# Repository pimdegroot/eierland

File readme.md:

This is a prototype project and has been put online to help somebody out. There are known bugs and it is not recommend to replicate the board. At one point a new rev might appear.

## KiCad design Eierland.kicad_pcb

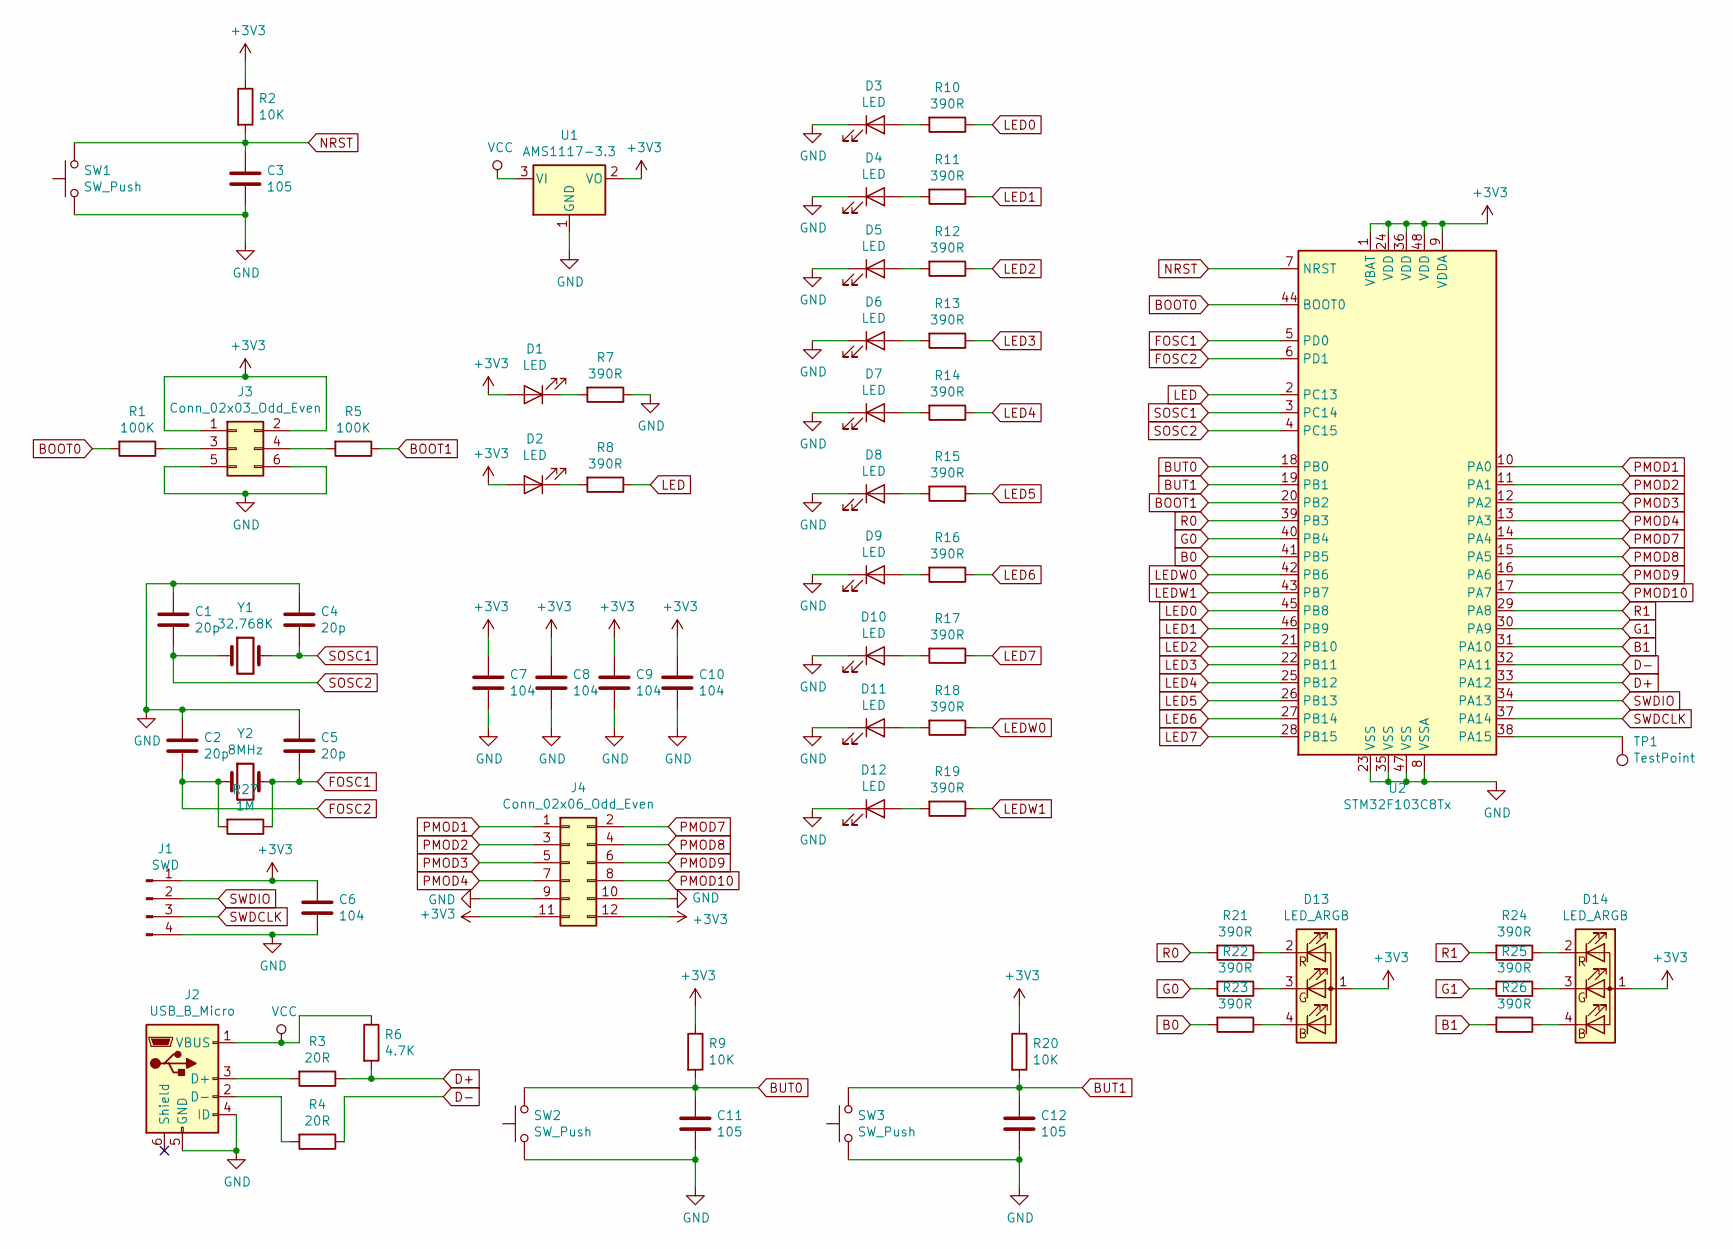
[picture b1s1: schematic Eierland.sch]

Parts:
C1, C2, C4, C5: 20p; C_0805_2012Metric
C3, C11, C12: 105; C_0805_2012Metric
C6, C7, C8, C9, C10: 104; C_0805_2012Metric
D1, D2, D3, D4, D5, D6, D7, D8, D9, D10, D11, D12: LED; LED_1206_3216Metric
D13, D14: LED_ARGB; LED_Cree-PLCC4_3.2x2.8mm_CCW
J1: SWD; PinHeader_1x04_P2.54mm_Horizontal
J2: USB_B_Micro; USB_Micro-B_GCT_USB3076-30-A
J3: Conn_02x03_Odd_Even; PinHeader_2x03_P2.54mm_Vertical
J4: Conn_02x06_Odd_Even; PinHeader_2x06_P2.54mm_Horizontal
R1, R5: 100K; R_0805_2012Metric
R2, R9, R20: 10K; R_0805_2012Metric
R3, R4: 20R; R_0805_2012Metric
R6: 4.7K; R_0805_2012Metric
R7, R8, R10, R11, R12, R13, R14, R15, R16, R17, R18, R19, R21, R22, R23, R24, R25, R26: 390R; R_0805_2012Metric
R27: 1M; R_0805_2012Metric
SW1, SW2, SW3: SW_Push; SW_SPST_EVPBF
TP1: TestPoint; TestPoint_Pad_D1.0mm
U1: AMS1117-3.3; SOT-223-3_TabPin2
U2: STM32F103C8Tx; LQFP-48_7x7mm_P0.5mm
Y1: 32.768K; Crystal_SMD_3215-2Pin_3.2x1.5mm
Y2: 8MHz; Crystal_SMD_HC49-SD

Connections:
+3V3: C6.1, C7.1, C8.1, C9.1, C10.1, D1.2 (A), D2.2 (A), D13.1 (A), D14.1 (A), J1.1, J3.1, J3.2, J4.11, J4.12, R2.1, R9.1, R20.1, U1.2 (VO), U2.1 (VBAT), U2.9 (VDDA), U2.24 (VDD), U2.36 (VDD), U2.48 (VDD)
B0: R23.2, U2.41 (PB5)
B1: R26.2, U2.31 (PA10)
BOOT0: R1.2, U2.44 (BOOT0)
BOOT1: R5.1, U2.20 (PB2)
BUT0: C11.1, R9.2, SW2.2, U2.18 (PB0)
BUT1: C12.1, R20.2, SW3.2, U2.19 (PB1)
D+: R3.1, R6.2, U2.33 (PA12)
D-: R4.1, U2.32 (PA11)
FOSC1: C5.2, R27.1, U2.5 (PD0), Y2.2
FOSC2: C2.2, R27.2, U2.6 (PD1), Y2.1
G0: R22.2, U2.40 (PB4)
G1: R25.2, U2.30 (PA9)
GND: C1.1, C2.1, C3.2, C4.1, C5.1, C6.2, C7.2, C8.2, C9.2, C10.2, C11.2, C12.2, D3.1 (K), D4.1 (K), D5.1 (K), D6.1 (K), D7.1 (K), D8.1 (K), D9.1 (K), D10.1 (K), D11.1 (K), D12.1 (K), J1.4, J2.4 (ID), J2.5 (GND), J3.5, J3.6, J4.9, J4.10, R7.1, SW1.1, SW2.1, SW3.1, U1.1 (GND), U2.8 (VSSA), U2.23 (VSS), U2.35 (VSS), U2.47 (VSS)
LED: R8.1, U2.2 (PC13)
LED0: R10.1, U2.45 (PB8)
LED1: R11.1, U2.46 (PB9)
LED2: R12.1, U2.21 (PB10)
LED3: R13.1, U2.22 (PB11)
LED4: R14.1, U2.25 (PB12)
LED5: R15.1, U2.26 (PB13)
LED6: R16.1, U2.27 (PB14)
LED7: R17.1, U2.28 (PB15)
LEDW0: R18.1, U2.42 (PB6)
LEDW1: R19.1, U2.43 (PB7)
NRST: C3.1, R2.2, SW1.2, U2.7 (NRST)
unnamed: D1.1 (K), R7.2
unnamed: D2.1 (K), R8.2
unnamed: D3.2 (A), R10.2
unnamed: D4.2 (A), R11.2
unnamed: D5.2 (A), R12.2
unnamed: D6.2 (A), R13.2
unnamed: D7.2 (A), R14.2
unnamed: D8.2 (A), R15.2
unnamed: D9.2 (A), R16.2
unnamed: D10.2 (A), R17.2
unnamed: D11.2 (A), R18.2
unnamed: D12.2 (A), R19.2
unnamed: D13.2 (RK), R21.1
unnamed: D13.3 (GK), R22.1
unnamed: D13.4 (BK), R23.1
unnamed: D14.2 (RK), R24.1
unnamed: D14.3 (GK), R25.1
unnamed: D14.4 (BK), R26.1
unnamed: J2.2 (D-), R4.2
unnamed: J2.3 (D+), R3.2
unnamed: J3.3, R1.1
unnamed: J3.4, R5.2
unnamed: TP1.1, U2.38 (PA15)
PMOD1: J4.1, U2.10 (PA0)
PMOD2: J4.3, U2.11 (PA1)
PMOD3: J4.5, U2.12 (PA2)
PMOD4: J4.7, U2.13 (PA3)
PMOD7: J4.2, U2.14 (PA4)
PMOD8: J4.4, U2.15 (PA5)
PMOD9: J4.6, U2.16 (PA6)
PMOD10: J4.8, U2.17 (PA7)
R0: R21.2, U2.39 (PB3)
R1: R24.2, U2.29 (PA8)
SOSC1: C4.2, U2.3 (PC14), Y1.2
SOSC2: C1.2, U2.4 (PC15), Y1.1
SWDCLK: J1.3, U2.37 (PA14)
SWDIO: J1.2, U2.34 (PA13)
VCC: J2.1 (VBUS), R6.1, U1.3 (VI)

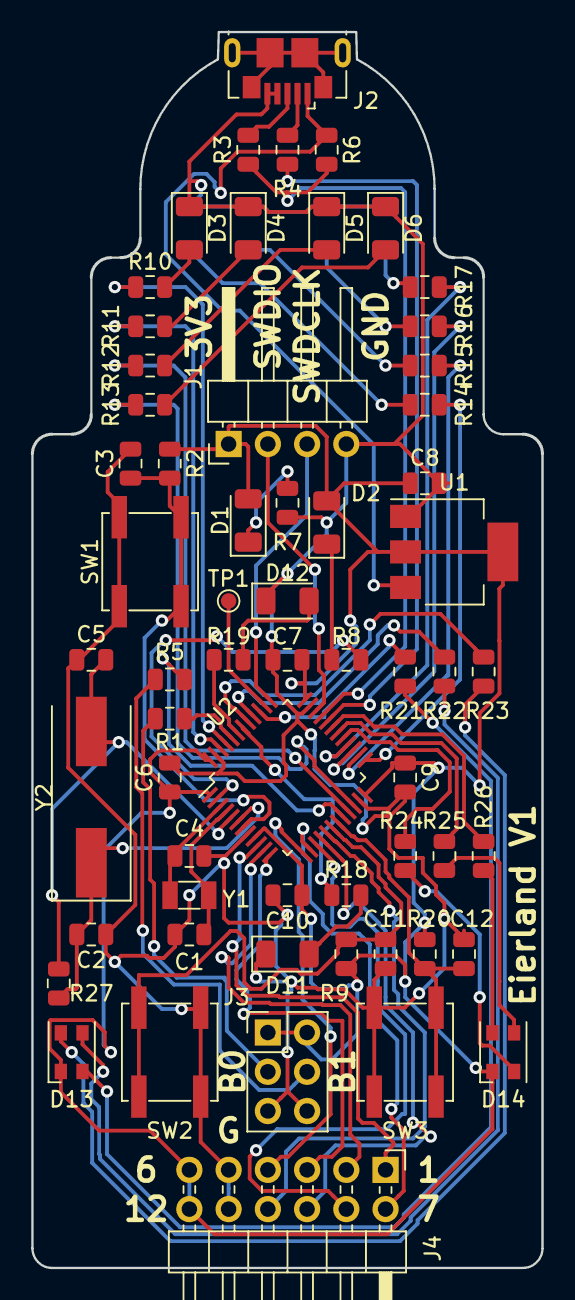
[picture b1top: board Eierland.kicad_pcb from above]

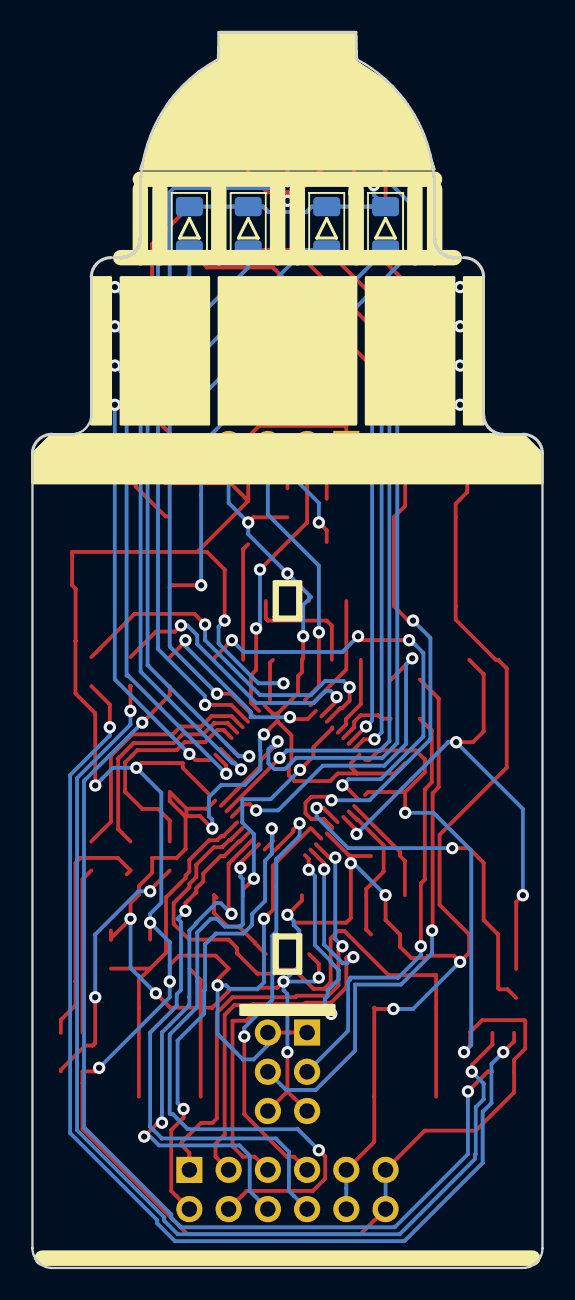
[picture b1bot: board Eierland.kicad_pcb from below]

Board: 2 copper layers, 33.0 x 80.0 mm, 65 parts (4 on the bottom side), 64 nets.

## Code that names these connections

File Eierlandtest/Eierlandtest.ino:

// the setup function runs once when you press reset or power the board
unsigned int rdelay;

void setup() {
  // initialize digital pin LED_BUILTIN as an output.
  Serial.begin(9600);
  pinMode(PB8, OUTPUT);
  pinMode(PB9, OUTPUT);
  pinMode(PB10, OUTPUT);
  pinMode(PB11, OUTPUT);
  pinMode(PB12, OUTPUT);
  pinMode(PB13, OUTPUT);
  pinMode(PB14, OUTPUT);
  pinMode(PB15, OUTPUT);

  pinMode(PB6, OUTPUT);
  pinMode(PB7, OUTPUT);

  pinMode(PA0, OUTPUT);
  pinMode(PA1, OUTPUT);
  pinMode(PA2, OUTPUT);
  pinMode(PA3, OUTPUT);
  pinMode(PA4, OUTPUT);
  pinMode(PA5, OUTPUT);
  pinMode(PA6, OUTPUT);
  pinMode(PA7, OUTPUT);

  digitalWrite(PB6, LOW);
  digitalWrite(PB7, LOW);
  delay(2000);
  digitalWrite(PB6, HIGH);
  delay(2000);
  digitalWrite(PB7,HIGH);

  rdelay = 20;

  
}

// the loop function runs over and over again forever
void loop() {
  
  
  digitalWrite(PA0, HIGH);
  digitalWrite(PB8,LOW);
  digitalWrite(PB9,LOW);
  digitalWrite(PB10,LOW);
  digitalWrite(PB11,LOW);
  digitalWrite(PB12,LOW);
  delay(rdelay);
  digitalWrite(PB13,LOW);
  delay(rdelay);
  digitalWrite(PB14,LOW);
  delay(rdelay);
  digitalWrite(PB15,LOW);

  delay(2000);
  digitalWrite(PA0, LOW);
  digitalWrite(PA1, HIGH);

  Serial.println("Blink");

  digitalWrite(PB11,HIGH);
  delay(rdelay);
  digitalWrite(PB10,HIGH);
  delay(rdelay);
  digitalWrite(PB9,HIGH);
  delay(rdelay);
  digitalWrite(PB8,HIGH);

  delay(1000);
  digitalWrite(PA1, LOW);
  digitalWrite(PA2, HIGH);

  digitalWrite(PB11,LOW);
  delay(rdelay);
  digitalWrite(PB10,LOW);
  delay(rdelay);
  digitalWrite(PB9,LOW);
  delay(rdelay);
  digitalWrite(PB8,LOW);

  delay(1000);
  digitalWrite(PA2, LOW);
  digitalWrite(PA3, HIGH);

  Serial.println("Blink");

  digitalWrite(PB11,HIGH);
  delay(rdelay);
  digitalWrite(PB10,HIGH);
  delay(rdelay);
  digitalWrite(PB9,HIGH);
  delay(rdelay);
  digitalWrite(PB8,HIGH);

  delay(1000);
  digitalWrite(PA3, LOW);
  digitalWrite(PA4, HIGH);

  digitalWrite(PB11,LOW);
  delay(rdelay);
  digitalWrite(PB10,LOW);
  delay(rdelay);
  digitalWrite(PB9,LOW);
  delay(rdelay);
  digitalWrite(PB8,LOW);

  delay(2000);
  digitalWrite(PA4, LOW);
  digitalWrite(PA5, HIGH);

  Serial.println("Blink");

  digitalWrite(PB12,HIGH);
  delay(rdelay);
  digitalWrite(PB13,HIGH);
  delay(rdelay);
  digitalWrite(PB14,HIGH);
  delay(rdelay);
  digitalWrite(PB15,HIGH);

  delay(1000);
  digitalWrite(PA5, LOW);
  digitalWrite(PA6, HIGH);

  digitalWrite(PB12,LOW);
  delay(rdelay);
  digitalWrite(PB13,LOW);
  delay(rdelay);
  digitalWrite(PB14,LOW);
  delay(rdelay);
  digitalWrite(PB15,LOW);

  delay(1000);
  digitalWrite(PA6, LOW);
  digitalWrite(PA7, HIGH);

  Serial.println("Blink");

  digitalWrite(PB12,HIGH);
  delay(rdelay);
  digitalWrite(PB13,HIGH);
  delay(rdelay);
  digitalWrite(PB14,HIGH);
  delay(rdelay);
  digitalWrite(PB15,HIGH);

  delay(1000);
  digitalWrite(PA7, LOW);
  
  
  
}

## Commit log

2019-12-30 Initial upload
